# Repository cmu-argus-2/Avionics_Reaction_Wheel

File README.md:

Equipment:
- DC Power Supply (set to 12V, 0.9A) 
- Nucleo-G474RE mircocontroller board
- MCF8315C motor driver (on MCF8315EVM board, use VBAT not VM)
- 2804 Three Phase Brushless Motor / AS5600 FOC Encoder (DFRobot, SKU: FIT1034)

Arduino IDE Setup:
- Need STM32 MCU based boards by STMircoelectronics board manager installed
- Select Tools > Board part number: > Nucleo G474RE
- Select Nucleo-64 from board & port menu

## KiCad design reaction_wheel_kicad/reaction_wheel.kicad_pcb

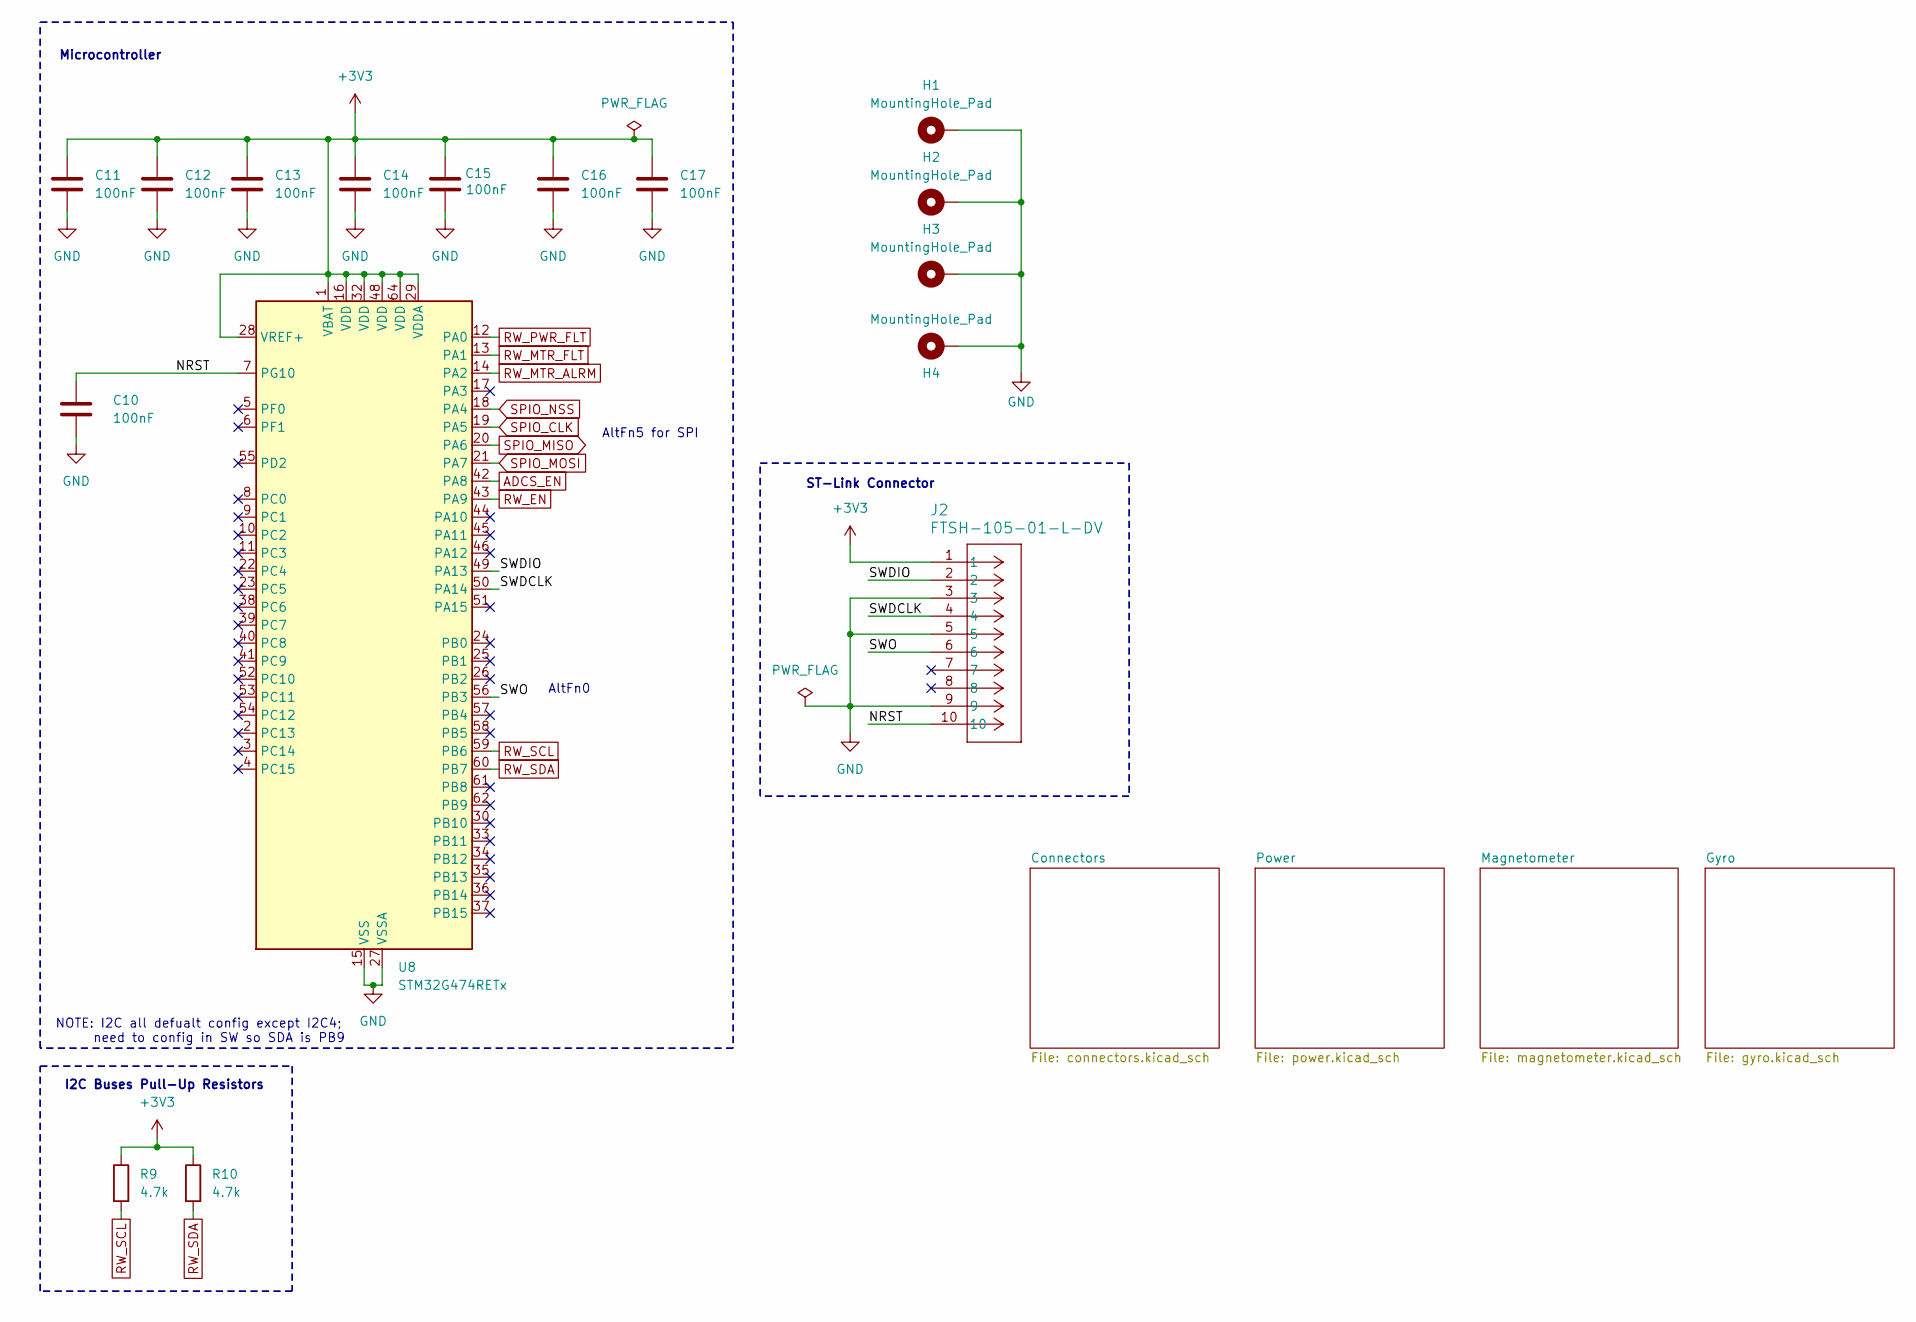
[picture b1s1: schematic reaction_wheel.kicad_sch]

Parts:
C10, C11, C12, C13, C14, C15, C16, C17: 100nF; C_0603_1608Metric
H1, H2, H3, H4: MountingHole_Pad; MountingHole_3.2mm_M3_Pad_Via
J2: FTSH-105-01-L-DV; CON10_2X5_DU_FTSH_SAI
R9, R10: 4.7k; R_0603_1608Metric
U8: STM32G474RETx; LQFP-64_10x10mm_P0.5mm

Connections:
+3V3: C11.1, C12.1, C13.1, C14.1, C15.1, C16.1, C17.1, J2.1, R9.1, R10.1, U8.1 (VBAT), U8.16 (VDD), U8.28 (VREF+), U8.29 (VDDA), U8.32 (VDD), U8.48 (VDD), U8.64 (VDD); also elsewhere on the board
/NRST: C10.1, J2.10, U8.7 (PG10)
/SWDCLK: J2.4, U8.50 (PA14)
/SWDIO: J2.2, U8.49 (PA13)
/SWO: J2.6, U8.56 (PB3)
ADCS_EN: U8.42 (PA8); also elsewhere on the board
GND: C10.2, C11.2, C12.2, C13.2, C14.2, C15.2, C16.2, C17.2, H1.1 (1_1), H2.1 (1_1), H3.1 (1_1), H4.1 (1_1), J2.3, J2.5, J2.9, U8.15 (VSS), U8.27 (VSSA), U8.31 (VSS), U8.47 (VSS), U8.63 (VSS); also elsewhere on the board
RW_EN: U8.43 (PA9); also elsewhere on the board
RW_MTR_ALRM: U8.14 (PA2); also elsewhere on the board
RW_MTR_FLT: U8.13 (PA1); also elsewhere on the board
RW_PWR_FLT: U8.12 (PA0); also elsewhere on the board
RW_SCL: R9.2, U8.59 (PB6); also elsewhere on the board
RW_SDA: R10.2, U8.60 (PB7); also elsewhere on the board
SPIO_CLK: U8.19 (PA5); also elsewhere on the board
SPIO_MISO: U8.20 (PA6); also elsewhere on the board
SPIO_MOSI: U8.21 (PA7); also elsewhere on the board
SPIO_NSS: U8.18 (PA4); also elsewhere on the board

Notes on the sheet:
Microcontroller
AltFn5 for SPI
NOTE: I2C all defualt config except I2C4; need to config in SW so SDA is PB9
ST-Link Connector
AltFn0
I2C Buses Pull-Up Resistors

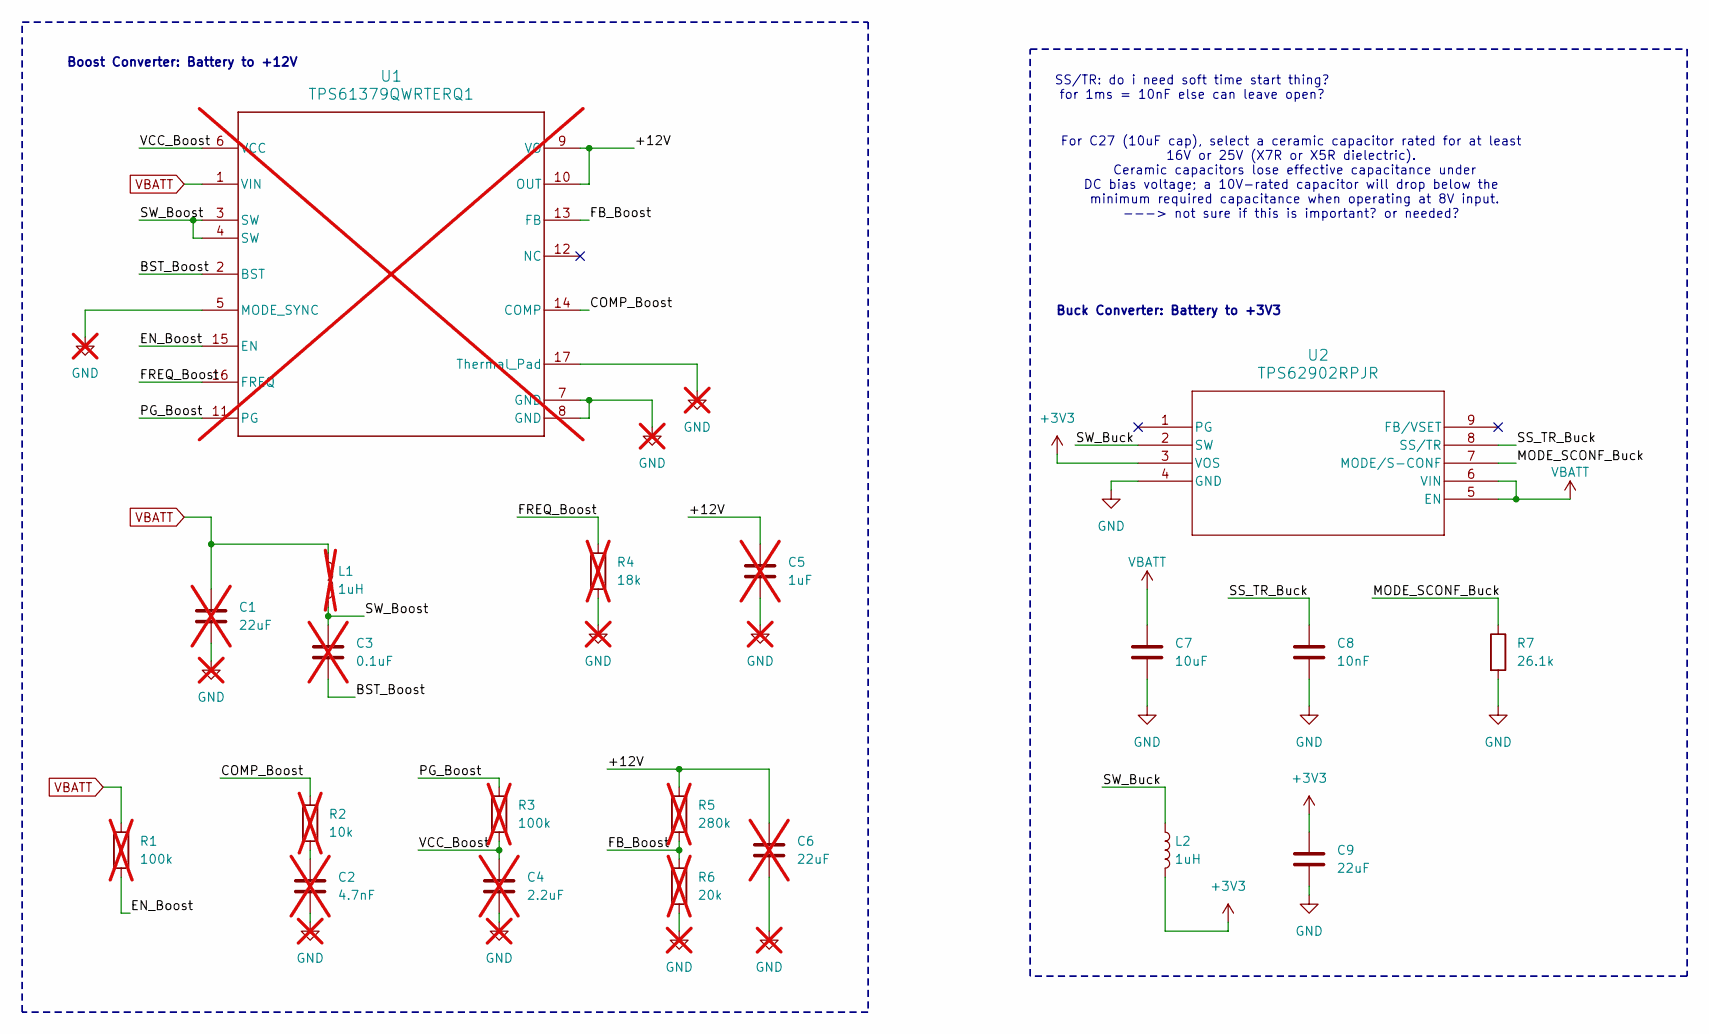
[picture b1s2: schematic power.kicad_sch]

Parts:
C1, C6: 22uF; C_0603_1608Metric; not fitted
C2: 4.7nF; C_0603_1608Metric; not fitted
C3: 0.1uF; C_0603_1608Metric; not fitted
C4: 2.2uF; C_0603_1608Metric; not fitted
C5: 1uF; C_0603_1608Metric; not fitted
C7: 10uF; C_0603_1608Metric
C8: 10nF; C_0603_1608Metric
C9: 22uF; C_0603_1608Metric
L1: 1uH; L_0603_1608Metric; not fitted
L2: 1uH; L_0603_1608Metric
R1, R3: 100k; R_0603_1608Metric; not fitted
R2: 10k; R_0603_1608Metric; not fitted
R4: 18k; R_0603_1608Metric; not fitted
R5: 280k; R_0603_1608Metric; not fitted
R6: 20k; R_0603_1608Metric; not fitted
R7: 26.1k; R_0603_1608Metric
U1: TPS61379QWRTERQ1; RTE0016K-IPC_B; not fitted
U2: TPS62902RPJR; QFN_902RPJR_TEX

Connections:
+3V3: C9.1, L2.2, U2.3 (VOS); also elsewhere on the board
/Power/+12V: C5.1, C6.1, R5.1, U1.9 (VO), U1.10 (OUT)
/Power/BST_Boost: C3.2, U1.2 (BST)
/Power/COMP_Boost: R2.1, U1.14 (COMP)
/Power/EN_Boost: R1.2, U1.15 (EN)
/Power/FB_Boost: R5.2, R6.1, U1.13 (FB)
/Power/FREQ_Boost: R4.1, U1.16 (FREQ)
/Power/MODE_SCONF_Buck: R7.1, U2.7 (MODE/S-CONF)
/Power/PG_Boost: R3.1, U1.11 (PG)
/Power/SS_TR_Buck: C8.1, U2.8 (SS/TR)
/Power/SW_Boost: C3.1, L1.2, U1.3 (SW), U1.4 (SW)
/Power/SW_Buck: L2.1, U2.2 (SW)
/Power/VCC_Boost: C4.1, R3.2, U1.6 (VCC)
GND: C1.2, C2.2, C4.2, C5.2, C6.2, C7.2, C8.2, C9.2, R4.2, R6.2, R7.2, U1.5 (MODE_SYNC), U1.7 (GND), U1.8 (GND), U1.17 (Thermal_Pad), U2.4 (GND); also elsewhere on the board
unnamed: C2.1, R2.2
VBATT: C1.1, C7.1, L1.1, R1.1, U1.1 (VIN), U2.5 (EN), U2.6 (VIN); also elsewhere on the board

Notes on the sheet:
Boost Converter: Battery to +12V
For C27 (10uF cap), select a ceramic capacitor rated for at least 16V or 25V (X7R or X5R dielectric). Ceramic capacitors lose effective capacitance under DC bias voltage; a 10V-rated capacitor will drop below the minimum required capacitance when operating at 8V input. ---> not sure if this is impo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
SS/TR: do i need soft time start thing? for 1ms = 10nF else can leave open?
Buck Converter: Battery to +3V3

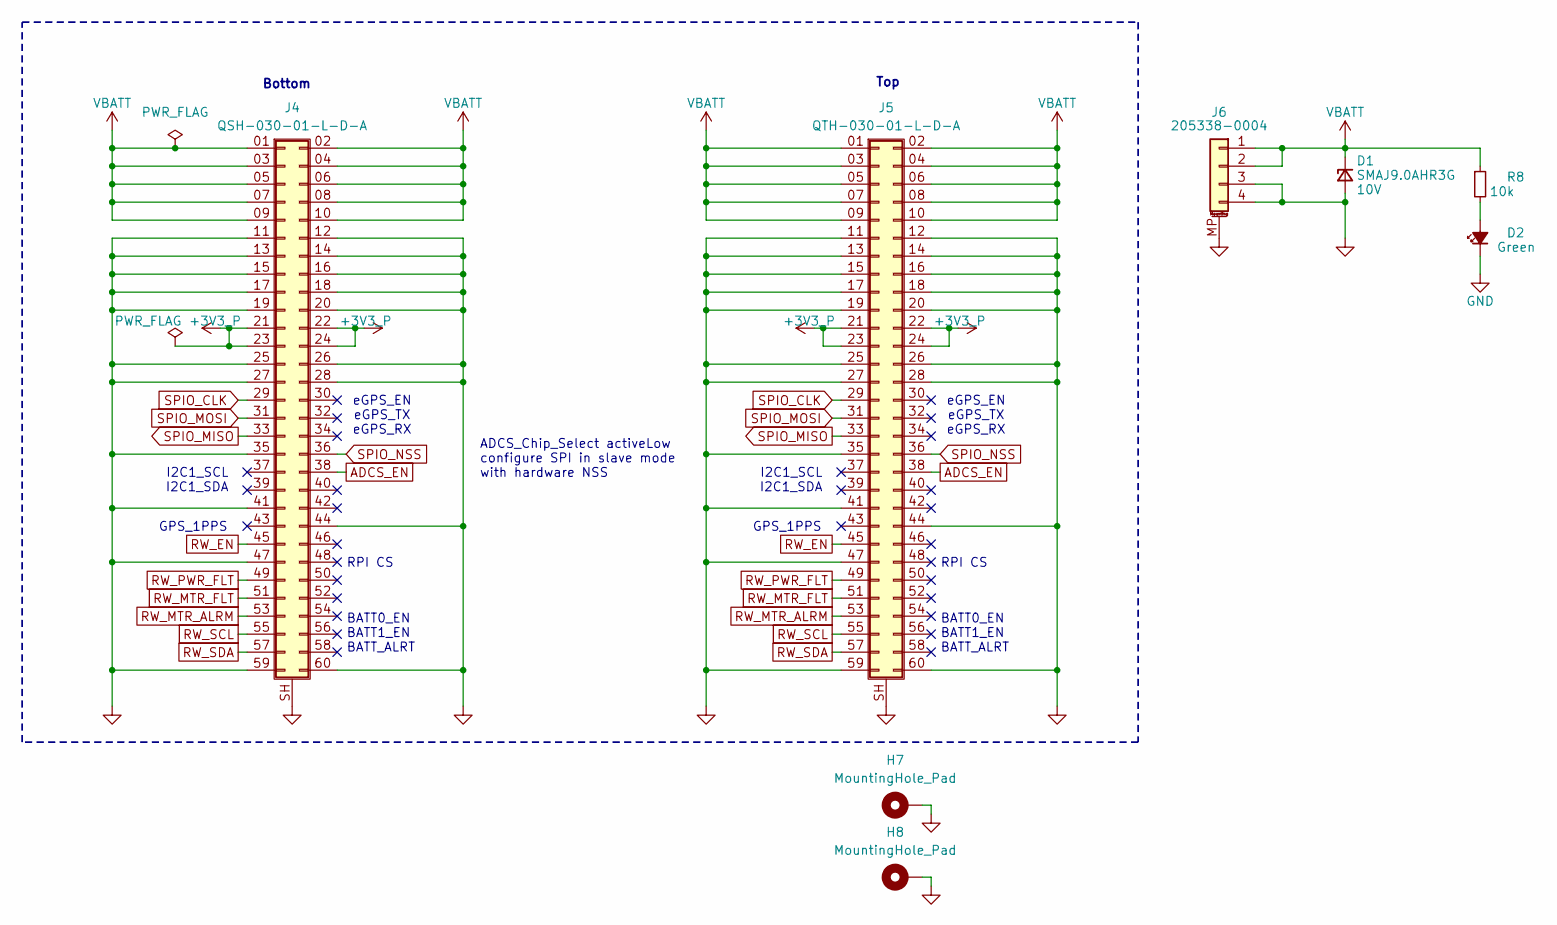
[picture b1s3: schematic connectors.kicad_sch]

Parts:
D1: SMAJ9.0AHR3G; D_SMA; Part 10V
D2: LED_G_0603_LTST-C190GKT; LED_0603_1608Metric; MPN C2909774
H7, H8: MountingHole_Pad; MountingHole_2.5mm_Pad_Via
J4: QSH-030-01-L-D-A; SAMTEC_QSH-030-01-L-D-A
J5: QTH-030-01-L-D-A; SAMTEC-QTH-030-01-X-D-A
J6: 205338-0004; Molex_Pico-Lock_205338-0004_1x04-1MP_P2.00mm_Horizontal; MPN C916325; LCSC C916325
R8: 10k; R_0603_1608Metric; MPN C2479067

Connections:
+3V3_P: J4.21, J4.22, J4.23, J4.24, J5.21, J5.22, J5.23, J5.24
ADCS_EN: J4.38, J5.38; also elsewhere on the board
GND: D1.2 (A), D2.1 (K), H7.1 (1_1), H8.1 (1_1), J4.11, J4.12, J4.13, J4.14, J4.15, J4.16, J4.17, J4.18, J4.19, J4.20, J4.25, J4.26, J4.27, J4.28, J4.35, J4.41, J4.44, J4.47, J4.59, J4.60, J4.SH (Shield), J5.11, J5.12, J5.13, J5.14, J5.15, J5.16, J5.17, J5.18, J5.19, J5.20, J5.25, J5.26, J5.27, J5.28, J5.35, J5.41, J5.44, J5.47, J5.59, J5.60, J5.SH (Shield), J6.3, J6.4, J6.MP (MountPin); also elsewhere on the board
unnamed: D2.2 (A), R8.2
RW_EN: J4.45, J5.45; also elsewhere on the board
RW_MTR_ALRM: J4.53, J5.53; also elsewhere on the board
RW_MTR_FLT: J4.51, J5.51; also elsewhere on the board
RW_PWR_FLT: J4.49, J5.49; also elsewhere on the board
RW_SCL: J4.55, J5.55; also elsewhere on the board
RW_SDA: J4.57, J5.57; also elsewhere on the board
SPIO_CLK: J4.29, J5.29; also elsewhere on the board
SPIO_MISO: J4.33, J5.33; also elsewhere on the board
SPIO_MOSI: J4.31, J5.31; also elsewhere on the board
SPIO_NSS: J4.36, J5.36; also elsewhere on the board
VBATT: D1.1 (K), J4.01 (Pin_1), J4.02 (Pin_2), J4.03 (Pin_3), J4.04 (Pin_4), J4.05 (Pin_5), J4.06 (Pin_6), J4.07 (Pin_7), J4.08 (Pin_8), J4.09 (Pin_9), J4.10, J5.01 (Pin_1), J5.02 (Pin_2), J5.03 (Pin_3), J5.04 (Pin_4), J5.05 (Pin_5), J5.06 (Pin_6), J5.07 (Pin_7), J5.08 (Pin_8), J5.09 (Pin_9), J5.10, J6.1, J6.2, R8.1; also elsewhere on the board

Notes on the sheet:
GPS_1PPS
RPI CS
I2C1_SCL I2C1_SDA
eGPS_EN eGPS_TX eGPS_RX
BATT0_EN BATT1_EN BATT_ALRT
Top
ADCS_Chip_Select activeLow configure SPI in slave mode with hardware NSS
Bottom

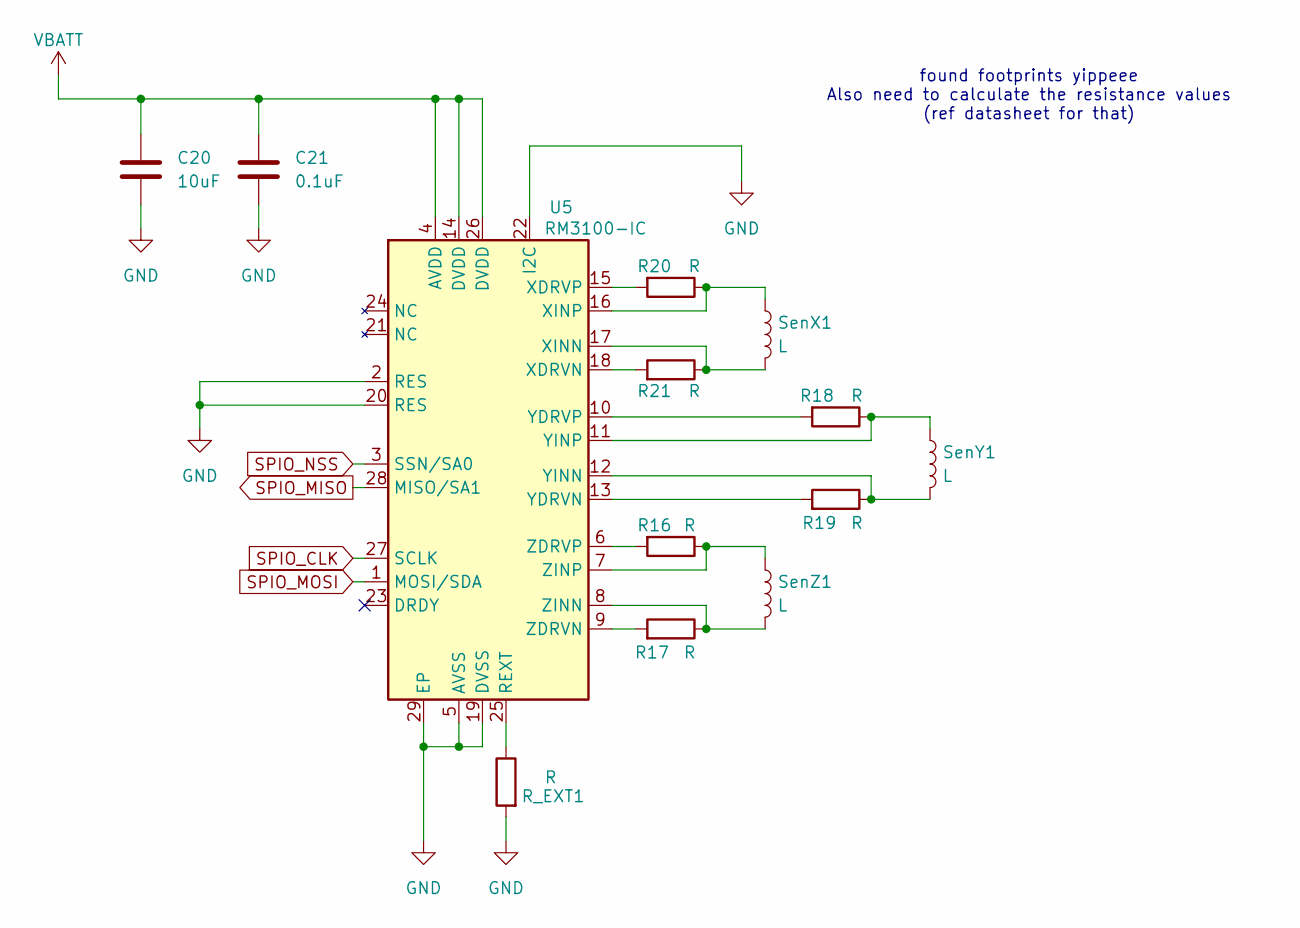
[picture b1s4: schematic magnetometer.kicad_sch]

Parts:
C20: 10uF; C_0603_1608Metric
C21: 0.1uF; C_0603_1608Metric
R16, R17, R18, R19, R20, R21: R; R_0603_1608Metric
R_EXT1: R; R_0603_1608Metric
SenX1: L; RM3100 SEN-XY-f
SenY1: L; RM3100 SEN-XY-f
SenZ1: L; RM3100 SEN-Z-f
U5: RM3100-IC; U-PNI-RM3100-IC

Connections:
GND: C20.2, C21.2, R_EXT1.2, U5.2 (RES), U5.5 (AVSS), U5.19 (DVSS), U5.20 (RES), U5.22 (I2C), U5.29 (EP); also elsewhere on the board
unnamed: R_EXT1.1, U5.25 (REXT)
unnamed: R21.2, U5.18 (XDRVN)
unnamed: R20.2, U5.15 (XDRVP)
unnamed: R21.1, SenX1.2, U5.17 (XINN)
unnamed: R20.1, SenX1.1, U5.16 (XINP)
unnamed: R19.2, U5.13 (YDRVN)
unnamed: R18.2, U5.10 (YDRVP)
unnamed: R19.1, SenY1.2, U5.12 (YINN)
unnamed: R18.1, SenY1.1, U5.11 (YINP)
unnamed: R17.2, U5.9 (ZDRVN)
unnamed: R16.2, U5.6 (ZDRVP)
unnamed: R17.1, SenZ1.2, U5.8 (ZINN)
unnamed: R16.1, SenZ1.1, U5.7 (ZINP)
SPIO_CLK: U5.27 (SCLK); also elsewhere on the board
SPIO_MISO: U5.28 (MISO/SA1); also elsewhere on the board
SPIO_MOSI: U5.1 (MOSI/SDA); also elsewhere on the board
SPIO_NSS: U5.3 (SSN/SA0); also elsewhere on the board
VBATT: C20.1, C21.1, U5.4 (AVDD), U5.14 (DVDD), U5.26 (DVDD); also elsewhere on the board

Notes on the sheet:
found footprints yippeee Also need to calculate the resistance values (ref datasheet for that)

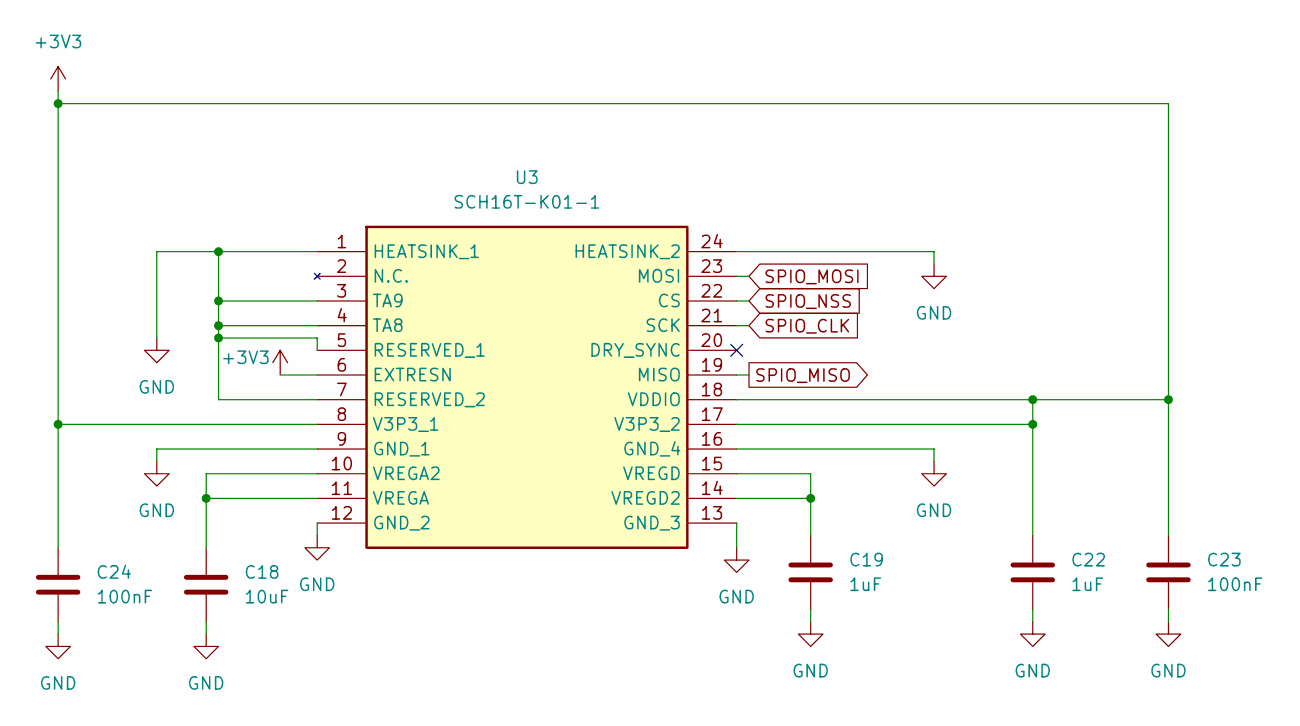
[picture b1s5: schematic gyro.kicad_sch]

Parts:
C18: 10uF; C_0603_1608Metric
C19, C22: 1uF; C_0603_1608Metric
C23, C24: 100nF; C_0603_1608Metric
U3: SCH16T-K01-1; SCH16TK011; Mouser Part Number 81-SCH16T-K01-1

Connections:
+3V3: C22.1, C23.1, C24.1, U3.6 (EXTRESN), U3.8 (V3P3_1), U3.17 (V3P3_2), U3.18 (VDDIO); also elsewhere on the board
GND: C18.2, C19.2, C22.2, C23.2, C24.2, U3.1 (HEATSINK_1), U3.3 (TA9), U3.4 (TA8), U3.5 (RESERVED_1), U3.7 (RESERVED_2), U3.9 (GND_1), U3.12 (GND_2), U3.13 (GND_3), U3.16 (GND_4), U3.24 (HEATSINK_2); also elsewhere on the board
unnamed: C18.1, U3.10 (VREGA2), U3.11 (VREGA)
unnamed: C19.1, U3.14 (VREGD2), U3.15 (VREGD)
SPIO_CLK: U3.21 (SCK); also elsewhere on the board
SPIO_MISO: U3.19 (MISO); also elsewhere on the board
SPIO_MOSI: U3.23 (MOSI); also elsewhere on the board
SPIO_NSS: U3.22 (CS); also elsewhere on the board

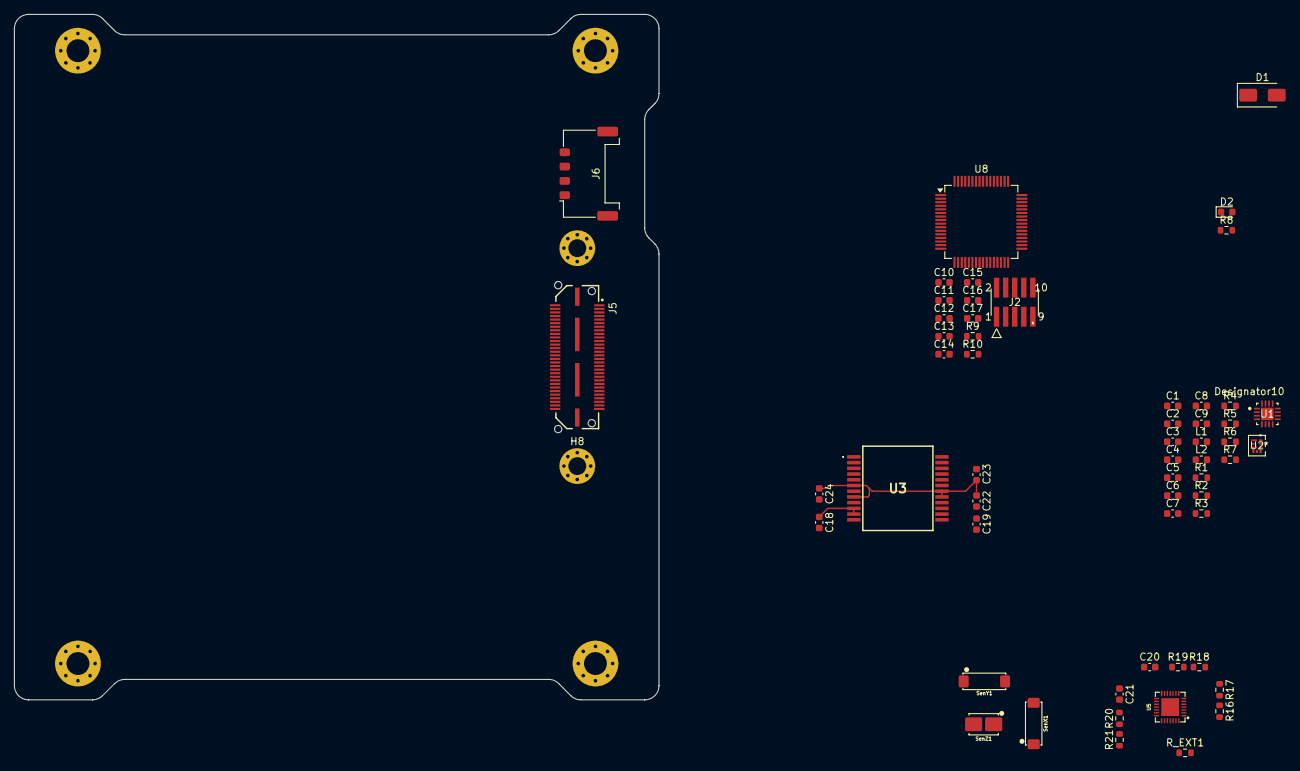
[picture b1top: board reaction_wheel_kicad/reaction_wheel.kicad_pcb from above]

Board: 4 copper layers, 90.2 x 95.9 mm, 63 parts (1 on the bottom side), 48 nets.

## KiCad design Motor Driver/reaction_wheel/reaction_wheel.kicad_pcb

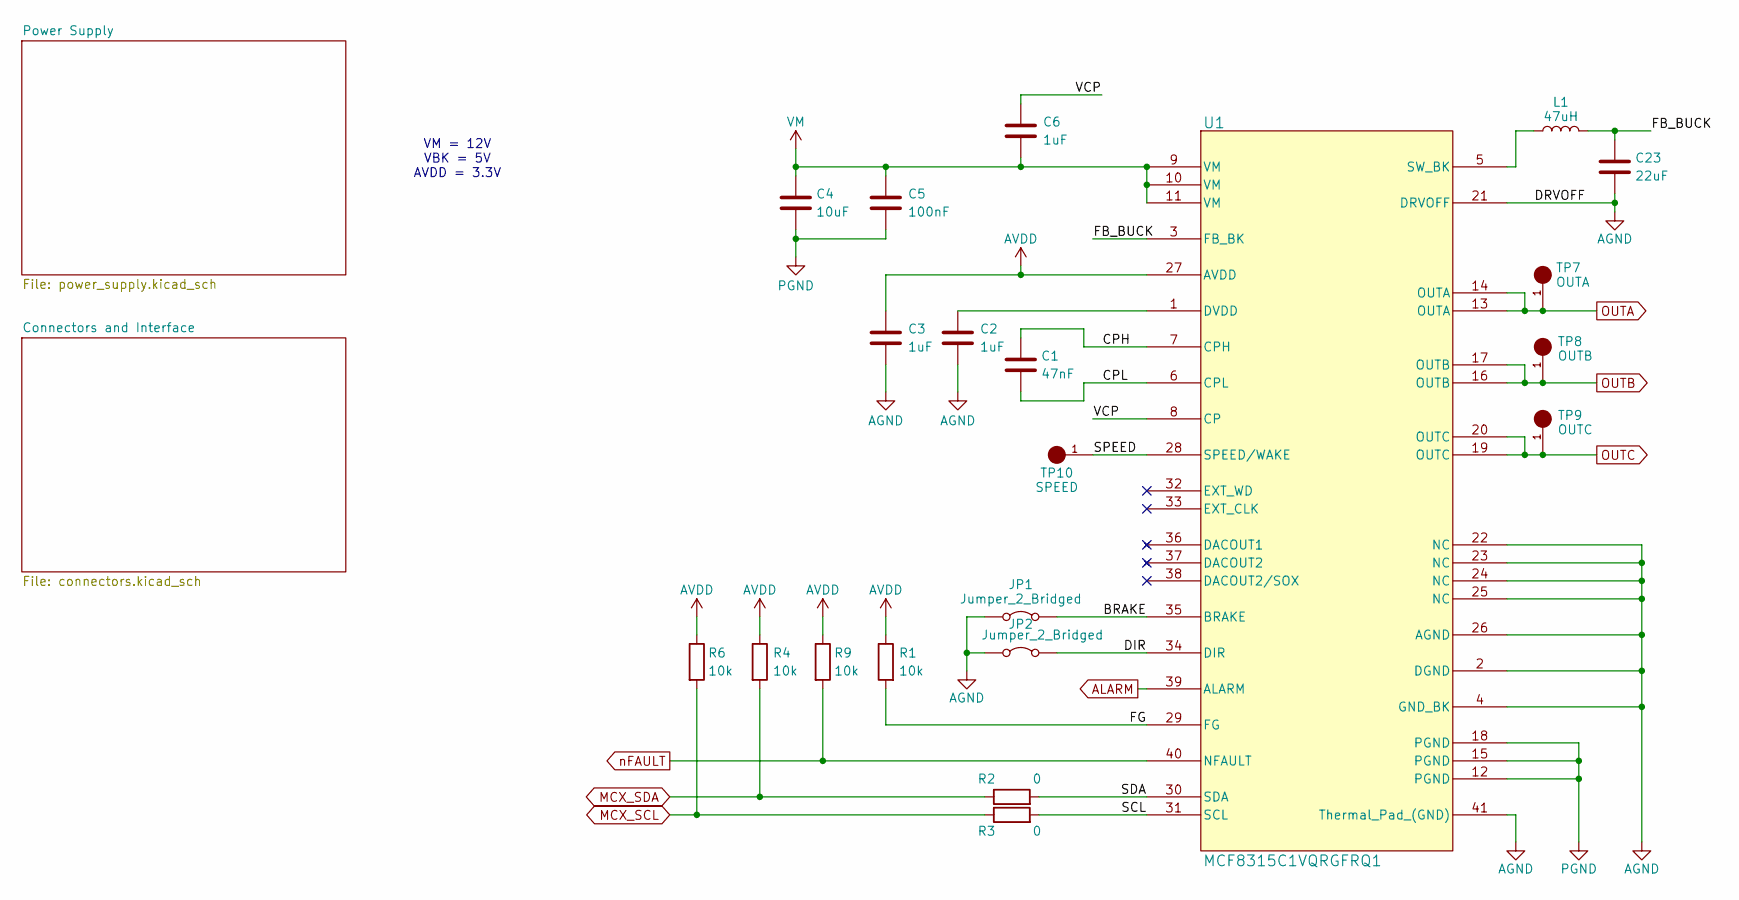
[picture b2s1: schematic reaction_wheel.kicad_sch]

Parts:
C1: 47nF; C_0603_1608Metric
C2, C3, C6: 1uF; C_0603_1608Metric
C4: 10uF; C_0805_2012Metric
C5: 100nF; C_0603_1608Metric
C23: 22uF; C_0603_1608Metric
JP1, JP2: Jumper_2_Bridged; SolderJumper-2_P1.3mm_Bridged_RoundedPad1.0x1.5mm
L1: 47uH; L_0603_1608Metric
R1, R4, R6, R9: 10k; R_0603_1608Metric
R2, R3: 0; R_0603_1608Metric
TP7: OUTA; TestPoint_Keystone_5000-5004_Miniature; MPN 5001; Digikey PN 36-5001-ND
TP8: OUTB; TestPoint_Keystone_5000-5004_Miniature; MPN 5001; Digikey PN 36-5001-ND
TP9: OUTC; TestPoint_Keystone_5000-5004_Miniature; MPN 5001; Digikey PN 36-5001-ND
TP10: SPEED; TestPoint_Keystone_5000-5004_Miniature; MPN 5001; Digikey PN 36-5001-ND
U1: MCF8315C1VQRGFRQ1; MCF8315C; MPN MCF8315C1VQRGFRQ1; Digikey PN 296-MCF8315C1VQRGFRQ1CT-ND

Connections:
/BRAKE: JP1.2 (B), U1.35 (BRAKE)
/CPH: C1.1, U1.7 (CPH)
/CPL: C1.2, U1.6 (CPL)
/DIR: JP2.2 (B), U1.34 (DIR)
/FB_BUCK: C23.1, L1.2, U1.3 (FB_BK)
/FG: R1.2, U1.29 (FG)
/SCL: R3.2, U1.31 (SCL)
/SDA: R2.2, U1.30 (SDA)
/SPEED: TP10.1, U1.28 (SPEED/WAKE)
/VCP: C6.1, U1.8 (CP)
AGND: C2.2, C3.2, C23.2, JP1.1 (A), JP2.1 (A), U1.2 (DGND), U1.4 (GND_BK), U1.21 (DRVOFF), U1.22 (NC), U1.23 (NC), U1.24 (NC), U1.25 (NC), U1.26 (AGND), U1.41 (Thermal_Pad_(GND)); also elsewhere on the board
ALARM: U1.39 (ALARM); also elsewhere on the board
AVDD: C3.1, R1.1, R4.1, R6.1, R9.1, U1.27 (AVDD)
MCX_SCL: R3.1, R6.2; also elsewhere on the board
MCX_SDA: R2.1, R4.2; also elsewhere on the board
unnamed: C2.1, U1.1 (DVDD)
unnamed: L1.1, U1.5 (SW_BK)
OUTA: TP7.1, U1.13 (OUTA), U1.14 (OUTA); also elsewhere on the board
OUTB: TP8.1, U1.16 (OUTB), U1.17 (OUTB); also elsewhere on the board
OUTC: TP9.1, U1.19 (OUTC), U1.20 (OUTC); also elsewhere on the board
PGND: C4.2, C5.2, U1.12 (PGND), U1.15 (PGND), U1.18 (PGND); also elsewhere on the board
VM: C4.1, C5.1, C6.2, U1.9 (VM), U1.10 (VM), U1.11 (VM); also elsewhere on the board
nFAULT: R9.2, U1.40 (NFAULT); also elsewhere on the board

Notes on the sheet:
VM = 12V VBK = 5V AVDD = 3.3V

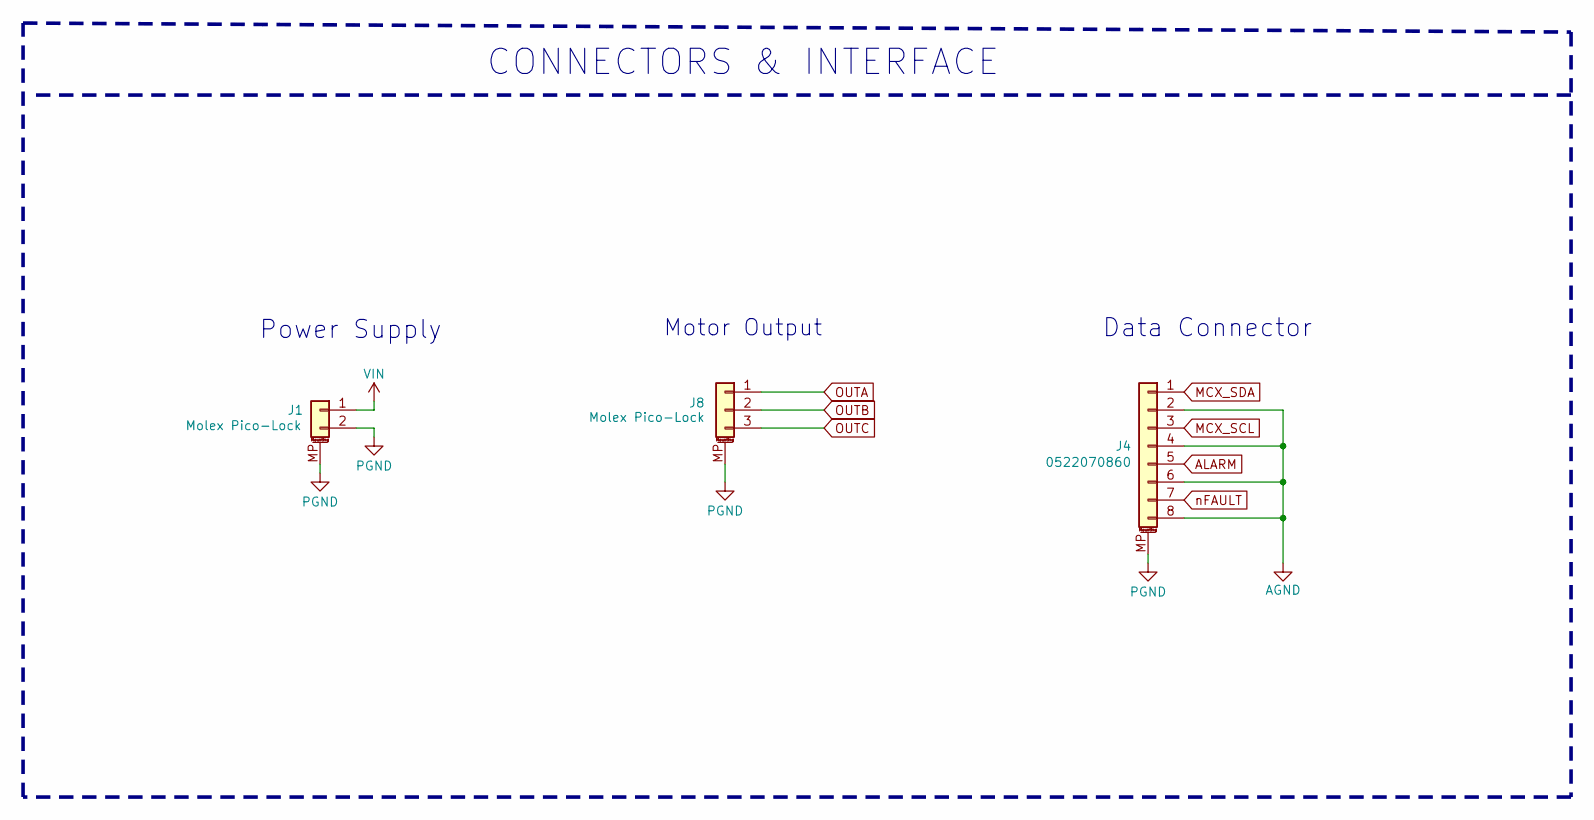
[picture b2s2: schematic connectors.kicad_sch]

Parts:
J1: Molex Pico-Lock; Molex_Pico-Lock_504050-0291_1x02-1MP_P1.50mm_Horizontal; Part Num 0781710002
J4: 0522070860; Molex 1x8 Right-Angle Conn; DigiKey PN 0522070860
J8: Molex Pico-Lock; Molex Pico-Lock 3 Socket Header; Part Number 0781710003

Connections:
AGND: J4.2, J4.4, J4.6, J4.8; also elsewhere on the board
ALARM: J4.5; also elsewhere on the board
MCX_SCL: J4.3; also elsewhere on the board
MCX_SDA: J4.1; also elsewhere on the board
OUTA: J8.1; also elsewhere on the board
OUTB: J8.2; also elsewhere on the board
OUTC: J8.3; also elsewhere on the board
PGND: J1.2, J1.MP (MountPin), J4.MP (MountPin), J8.MP (MountPin); also elsewhere on the board
VIN: J1.1; also elsewhere on the board
nFAULT: J4.7; also elsewhere on the board

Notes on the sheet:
CONNECTORS & INTERFACE
Data Connector
Motor Output
Power Supply

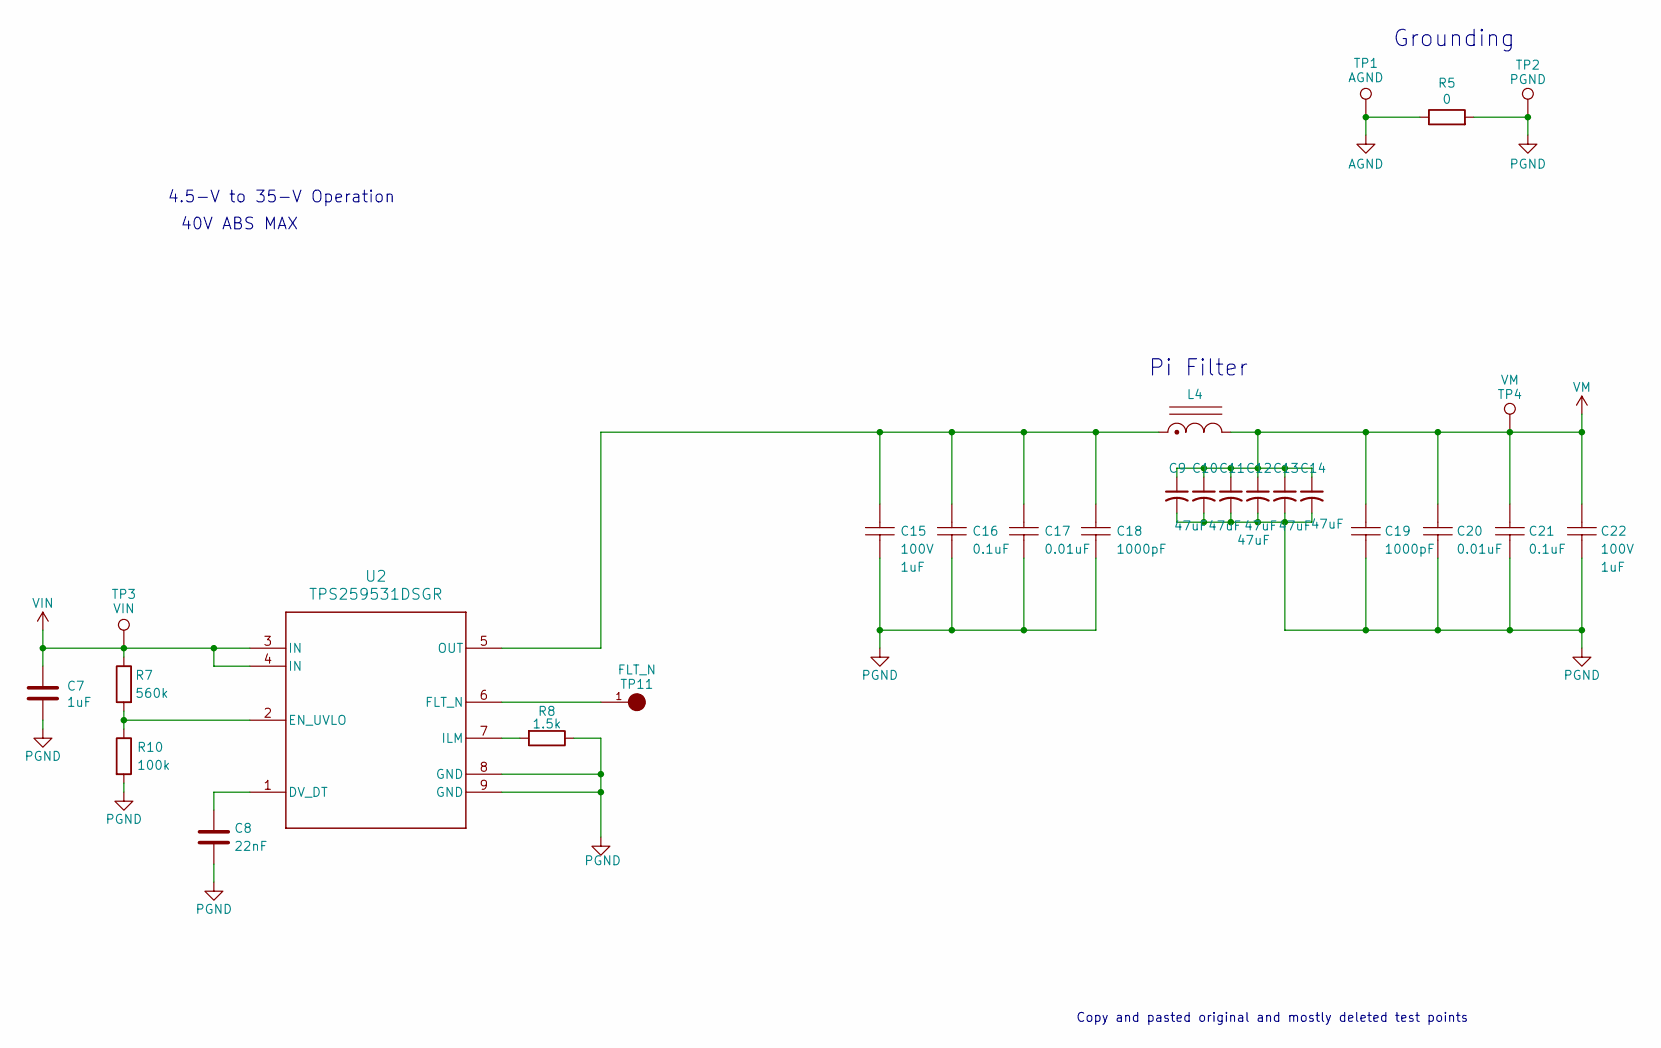
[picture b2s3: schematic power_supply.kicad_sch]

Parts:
C7: 1uF; C_0603_1608Metric
C8: 22nF; C_0603_1608Metric
C9, C10, C11, C12, C13, C14: 47uF; C_1206_3216Metric; DigiKey PN C3216X5R1E476M160AC
C15, C22: CGA3E3X7S2A104K080AB; C_0603_1608Metric; TOLERANCE_% 10%; PARTNUMBER CL31B105KCHNNNE
C16, C21: CGA3E3X7S2A104K080AB; C_0603_1608Metric; TOLERANCE_% 10%; PARTNUMBER CGA3E3X7S2A104K080AB
C17, C20: CGA3E2X7R2A103K080AA; C_0603_1608Metric; TOLERANCE_% 10%; PARTNUMBER CGA3E2X7R2A103K080AA
C18, C19: CGA3E2X7R2A102K080AA; C_0603_1608Metric; TOLERANCE_% 10%; PARTNUMBER CGA3E2X7R2A102K080AA
L4: XAL5030-102MEC; L_Coilcraft_XAL5030-XXX
R5: 0; R_0603_1608Metric
R7: 560k; R_0603_1608Metric
R8: 1.5k; R_0603_1608Metric
R10: 100k; R_0603_1608Metric
TP1: AGND; TestPoint_Keystone_5000-5004_Miniature
TP2: PGND; TestPoint_Keystone_5000-5004_Miniature
TP3: VIN; TestPoint_Keystone_5000-5004_Miniature
TP4: VM; TestPoint_Keystone_5000-5004_Miniature
TP11: FLT_N; TestPoint_Keystone_5000-5004_Miniature; MPN 5001; Digikey PN 36-5001-ND
U2: TPS259531DSGR; eFuse TPS259531DSGR_NV; Part Number TPS259531DSGR

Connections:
AGND: R5.1, TP1.1 (1_1); also elsewhere on the board
unnamed: C8.1, U2.1 (DV_DT)
unnamed: R7.2, R10.1, U2.2 (EN_UVLO)
unnamed: TP11.1, U2.6 (FLT_N)
unnamed: R8.2, U2.7 (ILM)
unnamed: C15.1, C16.1, C17.1, C18.1, L4.1, U2.5 (OUT)
PGND: C7.2, C8.2, C9.2, C10.2, C11.2, C12.2, C13.2, C14.2, C15.2, C16.2, C17.2, C18.2, C19.2, C20.2, C21.2, C22.2, R5.2, R8.1, R10.2, TP2.1 (1_1), U2.8 (GND), U2.9 (GND); also elsewhere on the board
VIN: C7.1, R7.1, TP3.1 (1_1), U2.3 (IN), U2.4 (IN); also elsewhere on the board
VM: C9.1, C10.1, C11.1, C12.1, C13.1, C14.1, C19.1, C20.1, C21.1, C22.1, L4.2, TP4.1 (1_1); also elsewhere on the board

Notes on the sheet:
40V ABS MAX
Grounding
Copy and pasted original and mostly deleted test points
Pi Filter
4.5-V to 35-V Operation

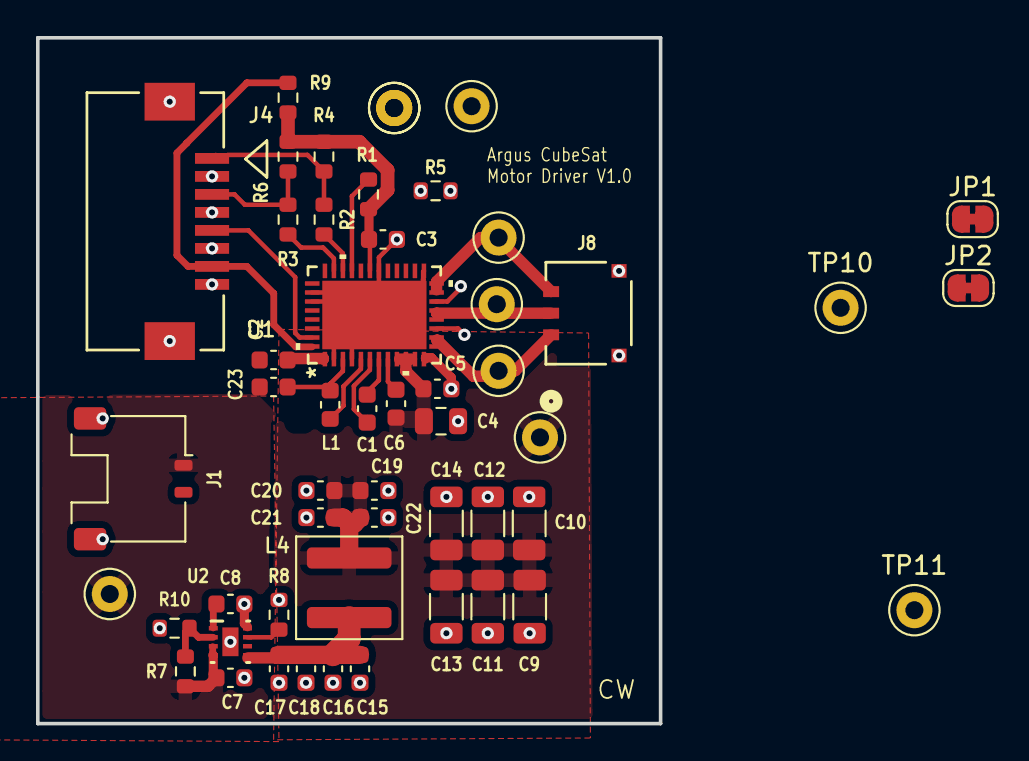
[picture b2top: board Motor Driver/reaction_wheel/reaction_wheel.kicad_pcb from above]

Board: 2 copper layers, 34.6 x 38.1 mm, 52 parts (0 on the bottom side), 29 nets.

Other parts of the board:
TP1#2: AGND; TestPoint_Keystone_5000-5004_Miniature

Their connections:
AGND: TP1#2.1 (1_1); also elsewhere on the board

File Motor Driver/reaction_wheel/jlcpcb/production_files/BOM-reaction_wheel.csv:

Comment,Designator,Footprint,LCSC,Quantity
0,"R2,R3,R5",R_0603_1608Metric,C1952,3
100k,R10,R_0603_1608Metric,C15458,1
100nF,C5,C_0603_1608Metric,C1591,1
10k,"R4,R6",R_0603_1608Metric,C15401,2
10uF,C4,C_0805_2012Metric,C15850,1
1500,R8,R_0603_1608Metric,C22843,1
1uF,"C2,C3,C6,C7",C_0603_1608Metric,C15849,4
22nF,C8,C_0603_1608Metric,C21122,1
22uF,C23,C_0603_1608Metric,C86295,1
47nF,C1,C_0603_1608Metric,C1622,1
47uH,L1,L_0603_1608Metric,C3910945,1
5.1k,"R1,R9",R_0603_1608Metric,C23186,2
560k,R7,R_0603_1608Metric,C23203,1
CGA3E2X7R2A102K080AA,"C18,C19",C_0603_1608Metric,C1588,2
CGA3E2X7R2A103K080AA,"C17,C20",C_0603_1608Metric,C1589,2
CGA3E3X7S2A104K080AB,"C15,C22",C_0603_1608Metric,C15849,2
CGA3E3X7S2A104K080AB,"C16,C21",C_0603_1608Metric,C1591,2
Data Conn,J4,Molex 1x8 Right-Angle Conn,C587867,1
Input Power,J1,Molex_Pico-Lock_504050-0291_1x02-1MP_P1.50mm_Horizontal,C5119943,1
MCF8315C1VQRGFRQ1,U1,MCF8315C,C31301704,1
MOTOR_OUT,J8,Molex Pico-Lock 3 Socket Header,C564183,1
TPS259531DSGR,U2,eFuse TPS259531DSGR_NV,C2155674,1
XAL5030-102MEC,L4,L_Coilcraft_XAL5030-XXX,C5379798,1

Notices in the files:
parts and their libraries:
License: Apache-2.0
